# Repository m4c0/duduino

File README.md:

# duduino

My own version of an Arduino-compatible board, with focus in SPI and IIC.

## Why another Arduino?

First and foremost, I'm not trying to "reinvent" or "improve" Arduino. I'm doing a lot of
experiments at home with "vanilla" Arduino. There may be some limitations, but usually it
is quite simple and fast to prototype.

Curiously, I don't need many GPIO ports - I interface using SPI or IIC, and that's it. So
all GPIOs are just hanging in there, doing nothing. Also, since some of those experiments
will be on my desk for a long time, it looks wasteful to leave Arduinos everywhere with
dupont cables (and I'm too lazy to rewire everything over and over when I do different
prototypes).

Therefore, I decided to design and solder my own boards, to fulfill my own requirements.
Since Arduino is Open-Source, I thought it's my duty to get my own Arduino and release it
as Open Source as well.

## Features

* Compatible with Arduino bootloaders
* Plug-and-play integration with FTDI USB-to-serial, AVRKit pins and IIC OLEDs
* SCL and SDA has stronger pull-ups
* Powered by USB (5V)
* Works at 3.3V (to avoid burning some OLEDs and FPGAs :)

## Limitations

* GPIOs are not exposed (except the ones for serial, SPI and IIC)
* Current version is THT, so the board is huge

## Things that may be added

* Powered by LiPo batteries. This depends if there'll be space left in the board

## Revision History

### Version v0.1 (in development)

* First release
* Contains:
  * USB connector
  * 8MHz crystal
  * LM3940 3.3V regulator
  * Inline pins for FTDI USB-to-Serial
  * Inline pins for IIC OLEDs
  * AVR-compatible SPI header
  * And the classic GPIO-13 LED

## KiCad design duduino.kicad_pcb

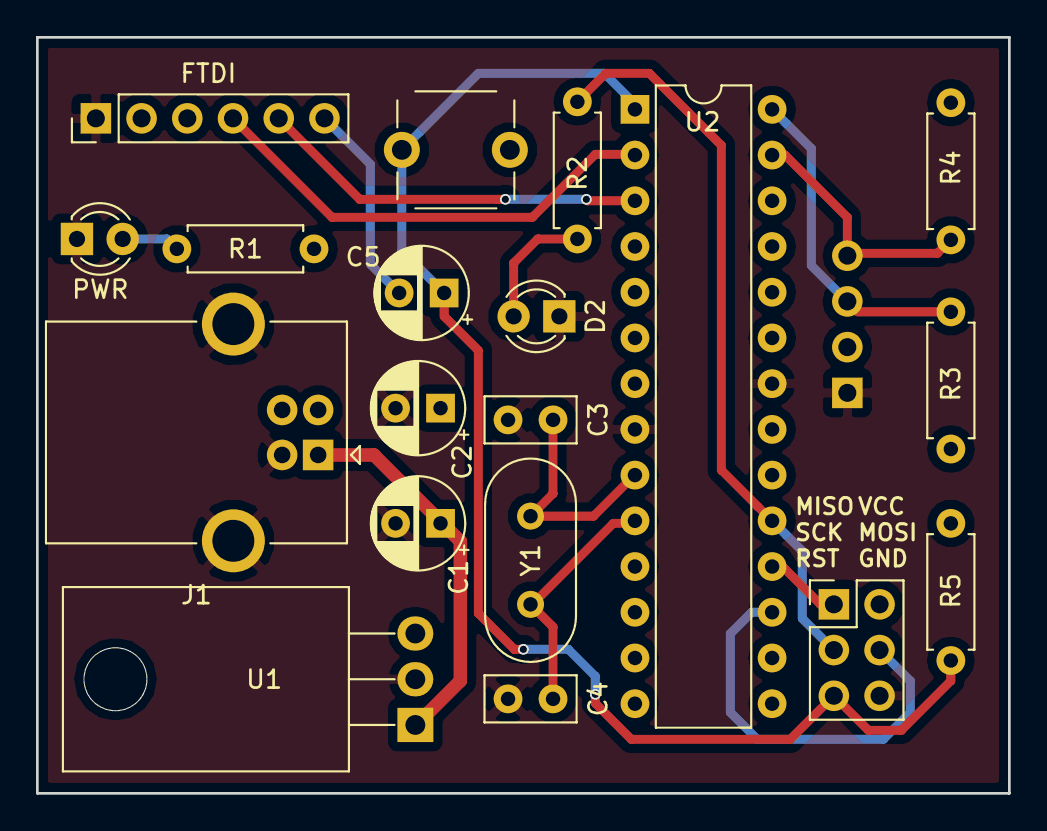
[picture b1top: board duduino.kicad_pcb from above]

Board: 2 copper layers, 54.0 x 42.0 mm, 20 parts (1 on the bottom side), 16 nets.

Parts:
C1: 0.47u; CP_Radial_D5.0mm_P2.50mm
C2: 33u; CP_Radial_D5.0mm_P2.50mm
C3, C4: 22p; C_Disc_D5.0mm_W2.5mm_P2.50mm
C5: 100n; CP_Radial_D5.0mm_P2.50mm
D1: PWR; LED_D3.0mm
D2: LED; LED_D3.0mm
J1: USB_B; USB_B_OST_USB-B1HSxx_Horizontal
J2: FTDI; PinHeader_1x06_P2.54mm_Vertical
J3: IIC; SPI-OLED
J4: AVRKit; PinHeader_2x03_P2.54mm_Vertical
R1, R2: 220; R_Axial_DIN0207_L6.3mm_D2.5mm_P7.62mm_Horizontal
R3, R4, R5: 10k; R_Axial_DIN0207_L6.3mm_D2.5mm_P7.62mm_Horizontal
SW1: RESET; SW_PUSH_6mm
U1: LM3940_TO220; TO-220-3_Horizontal_TabDown
U2: ATMEGA168-20PU; DIP-28_W7.62mm
Y1: Crystal; Crystal_HC18-U_Vertical

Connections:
+3V3: C2.1, J2.3, J3.2, J4.2, R1.2, R3.2, R4.2, R5.1, SW1.2, U1.3, U2.7, U2.20, U2.21
+5V: C1.1, J1.1, U1.1
/DTR: C5.2, J2.6
/I2C_SCL: J3.3, R3.1, U2.28
/I2C_SDA: J3.4, R4.1, U2.27
/MISO: J4.1, U2.18
/MOSI: J4.4, U2.17
/RST: C5.1, J4.5, R5.2, SW1.1, U2.1
/RXD: J2.4, U2.2
/SCK: J4.3, R2.2, U2.19
/TXD: J2.5, U2.3
/XTAL1: C3.1, U2.9, Y1.1
/XTAL2: C4.1, U2.10, Y1.2
GND: C1.2, C2.2, C3.2, C4.2, D1.1, D2.1, J1.4, J1.5, J2.1, J3.1, J4.6, U1.2, U2.8, U2.22
unnamed: D1.2, R1.1
unnamed: D2.2, R2.1

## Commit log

2018-07-13 added stubs for KiCAD + some thoughts on README
2018-07-13 first schematic
2018-07-18 assigning netlist and such
2018-07-18 playing around the layout of the pcb
2018-08-13 tweaking the layout, upgrading Kicad, crying a little bit, then wiring all the PCB
